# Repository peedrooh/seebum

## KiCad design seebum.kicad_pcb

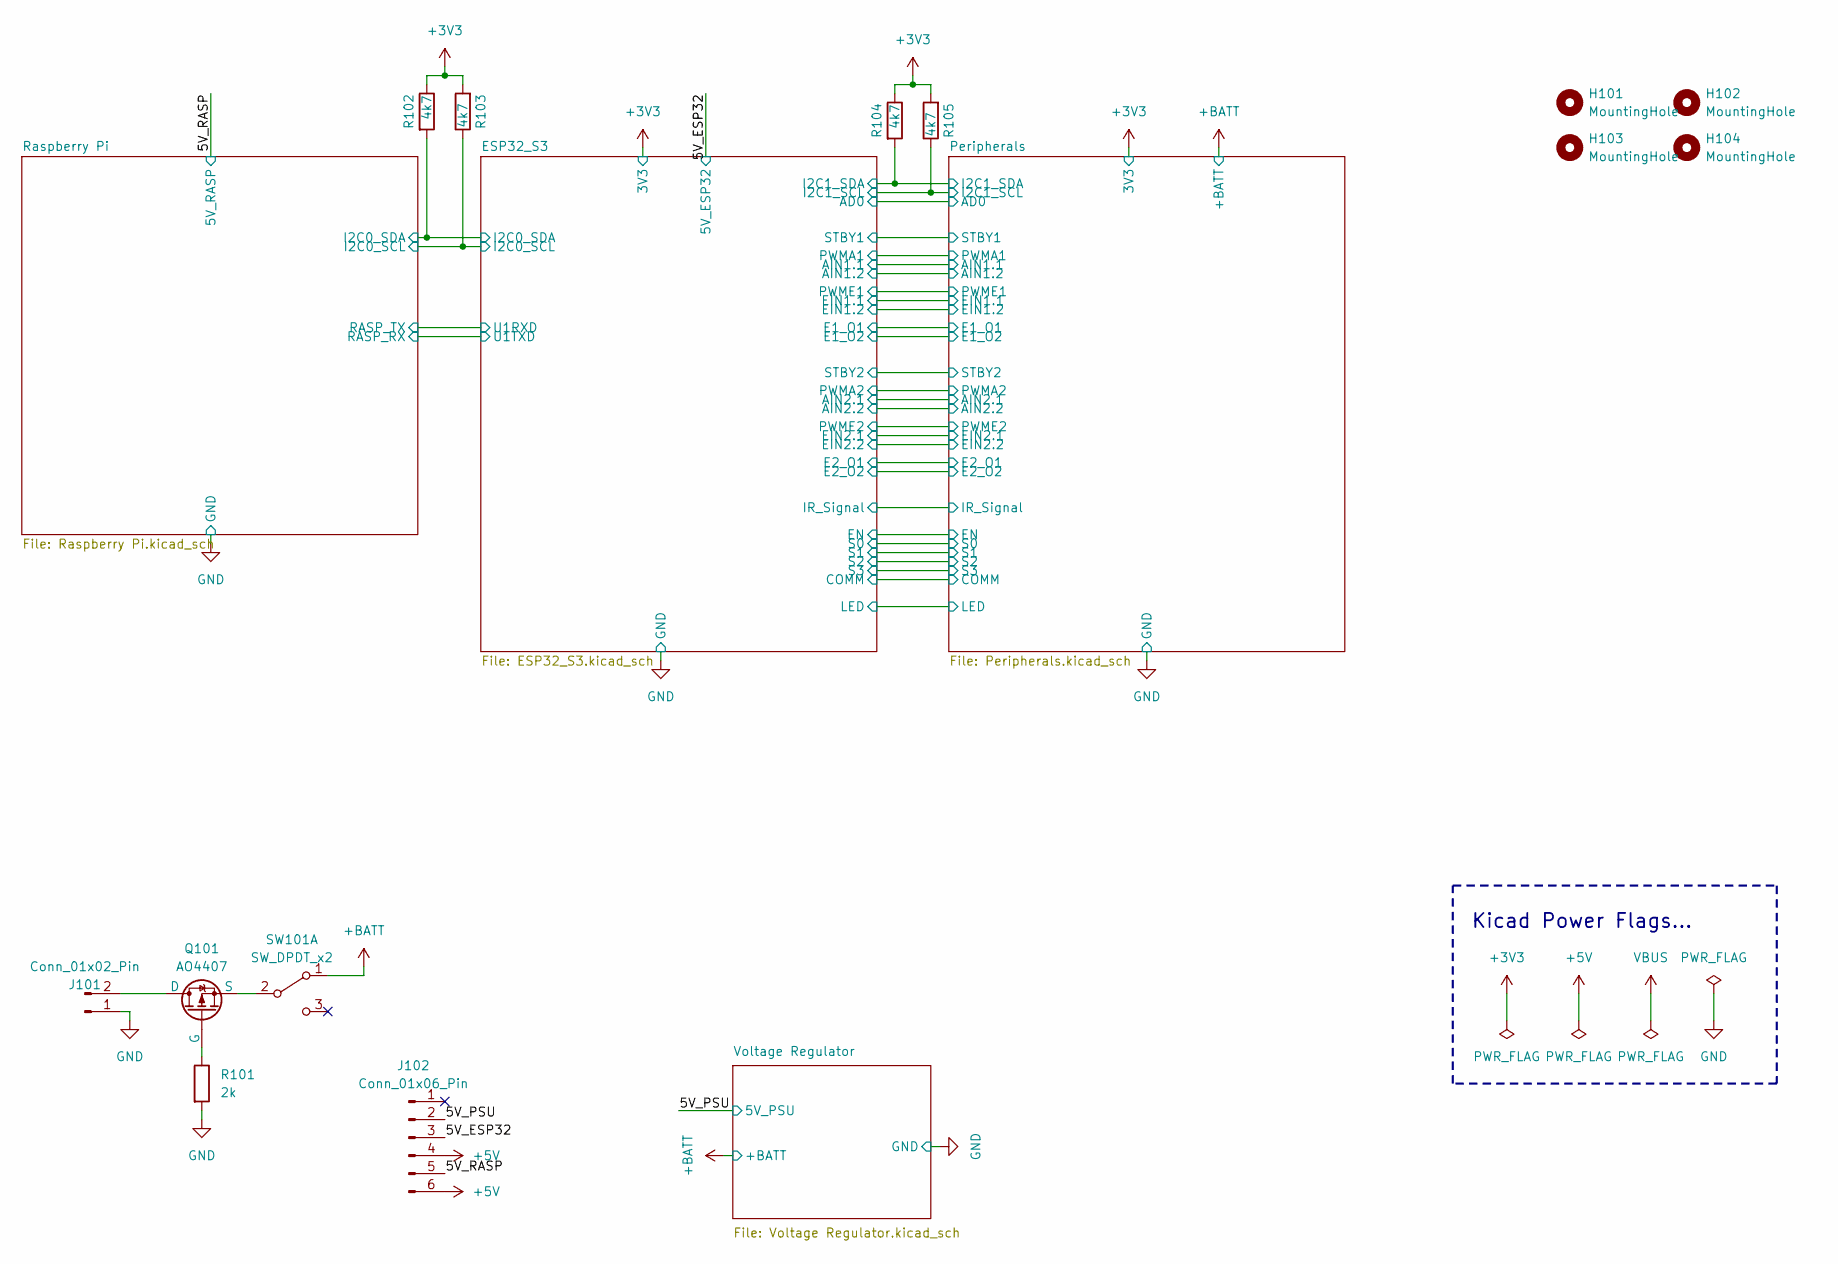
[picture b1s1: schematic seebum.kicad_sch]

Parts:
H101, H102, H103, H104: MountingHole; MountingHole_2.7mm_M2.5_Pad_Via
J101: Conn_01x02_Pin; AMASS_XT30PW-M_1x02_P2.50mm_Horizontal
J102: Conn_01x06_Pin; PinHeader_2x03_P2.54mm_Vertical
Q101: AO4407; SO-8_5.3x6.2mm_P1.27mm; LCSC C469397
R101: 2k; R_0805_2012Metric; LCSC C17604
R102, R103, R104, R105: 4k7; R_0805_2012Metric; LCSC C17673
SW101: SW_DPDT_x2; 5Amp_Switch; LCSC C2884744

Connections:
+3V3: R102.1, R103.2, R104.1, R105.2; also elsewhere on the board
+5V: J102.4, J102.6; also elsewhere on the board
+BATT: SW101.1 (A); also elsewhere on the board
/5V_ESP32: J102.3; also elsewhere on the board
/5V_PSU: J102.2; also elsewhere on the board
/5V_RASP: J102.5; also elsewhere on the board
/ESP32_S3/GPIO6: R102.2; also elsewhere on the board
/ESP32_S3/GPIO7: R103.1; also elsewhere on the board
/Peripherals/SCL: R105.1; also elsewhere on the board
/Peripherals/SDA: R104.2; also elsewhere on the board
GND: J101.1, R101.2; also elsewhere on the board
unnamed: J101.2, Q101.1 (D)
unnamed: Q101.2 (G), R101.1
unnamed: Q101.3 (S), SW101.2 (B)

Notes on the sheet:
Kicad Power Flags...

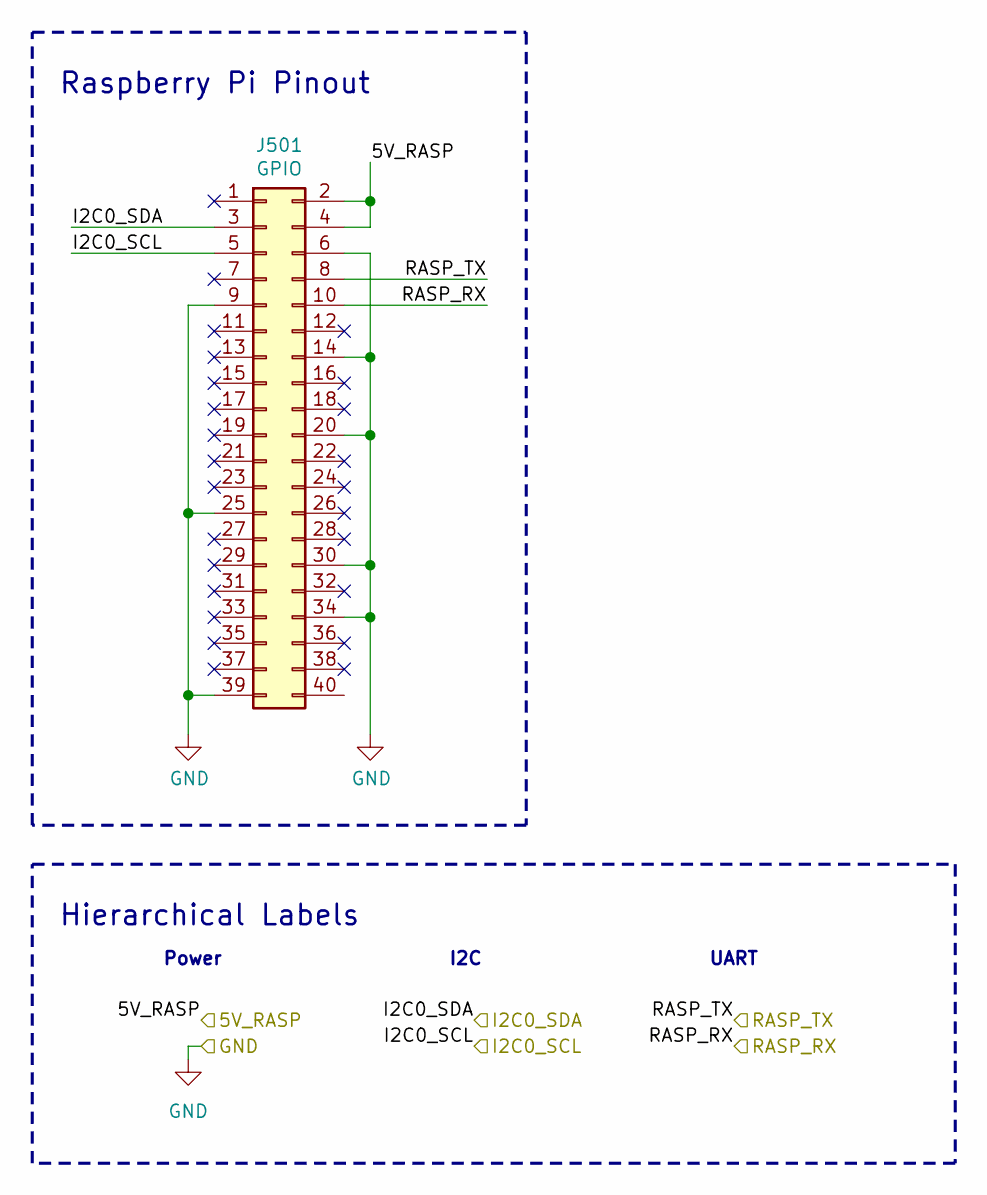
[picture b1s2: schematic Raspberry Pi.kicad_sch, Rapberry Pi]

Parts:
J501: GPIO; PinSocket_2x20_P2.54mm_Vertical

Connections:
/5V_RASP: J501.2, J501.4; also elsewhere on the board
/ESP32_S3/GPIO6: J501.3; also elsewhere on the board
/ESP32_S3/GPIO7: J501.5; also elsewhere on the board
/ESP32_S3/GPIO17: J501.10; also elsewhere on the board
/ESP32_S3/GPIO18: J501.8; also elsewhere on the board
GND: J501.6, J501.9, J501.14, J501.20, J501.25, J501.30, J501.34, J501.39; also elsewhere on the board

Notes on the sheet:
I2C
Hierarchical Labels
UART
Power
Raspberry Pi Pinout

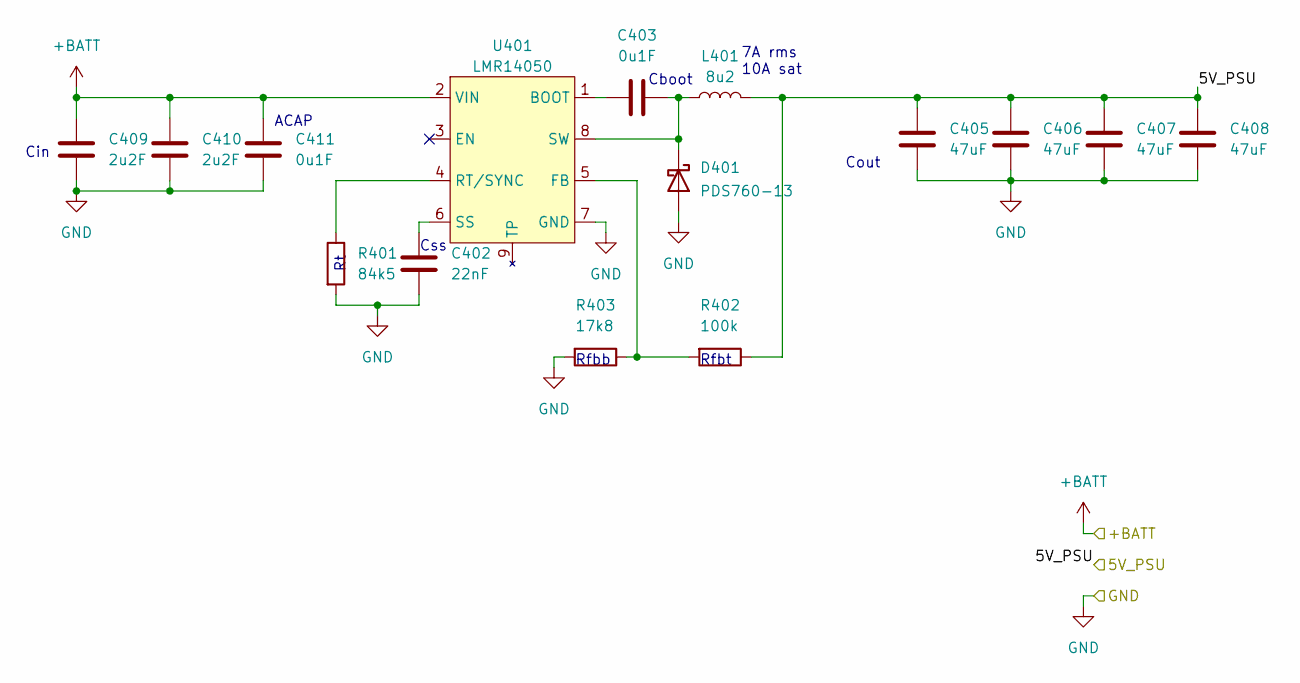
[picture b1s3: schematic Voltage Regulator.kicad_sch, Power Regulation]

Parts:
C402: 22nF; C_0805_2012Metric; LCSC C107137
C403, C411: 0u1F; C_0805_2012Metric; LCSC C89258
C405, C406, C407, C408: 47uF; C_0805_2012Metric; LCSC C7472975
C409, C410: 2u2F; C_1206_3216Metric; LCSC C577211
D401: PDS760-13; D_PowerDI-5; LCSC C96113
L401: 8u2; L_10.4x10.4_H4.8; LCSC C2847563
R401: 84k5; C_0805_2012Metric; LCSC C17842
R402: 100k; R_0805_2012Metric; LCSC C2763792
R403: 17k8; C_0805_2012Metric; LCSC C413729
U401: LMR14050; Texas_R-PDSO-G8_EP2.95x4.9mm_Mask2.4x3.1mm_ThermalVias; LCSC C155484

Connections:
+BATT: C409.1, C410.1, C411.1, U401.2 (VIN); also elsewhere on the board
/5V_PSU: C405.1, C406.1, C407.1, C408.1, L401.2, R402.1; also elsewhere on the board
GND: C402.2, C405.2, C406.2, C407.2, C408.2, C409.2, C410.2, C411.2, D401.2 (A), R401.2, R403.2, U401.7 (GND); also elsewhere on the board
unnamed: C403.2, D401.1 (K), L401.1, U401.8 (SW)
unnamed: C403.1, U401.1 (BOOT)
unnamed: R402.2, R403.1, U401.5 (FB)
unnamed: R401.1, U401.4 (RT/SYNC)
unnamed: C402.1, U401.6 (SS)

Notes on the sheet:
7A rms 10A sat
Cout
Cboot
ACAP
Cin
Css
Rfbt
Rfbb

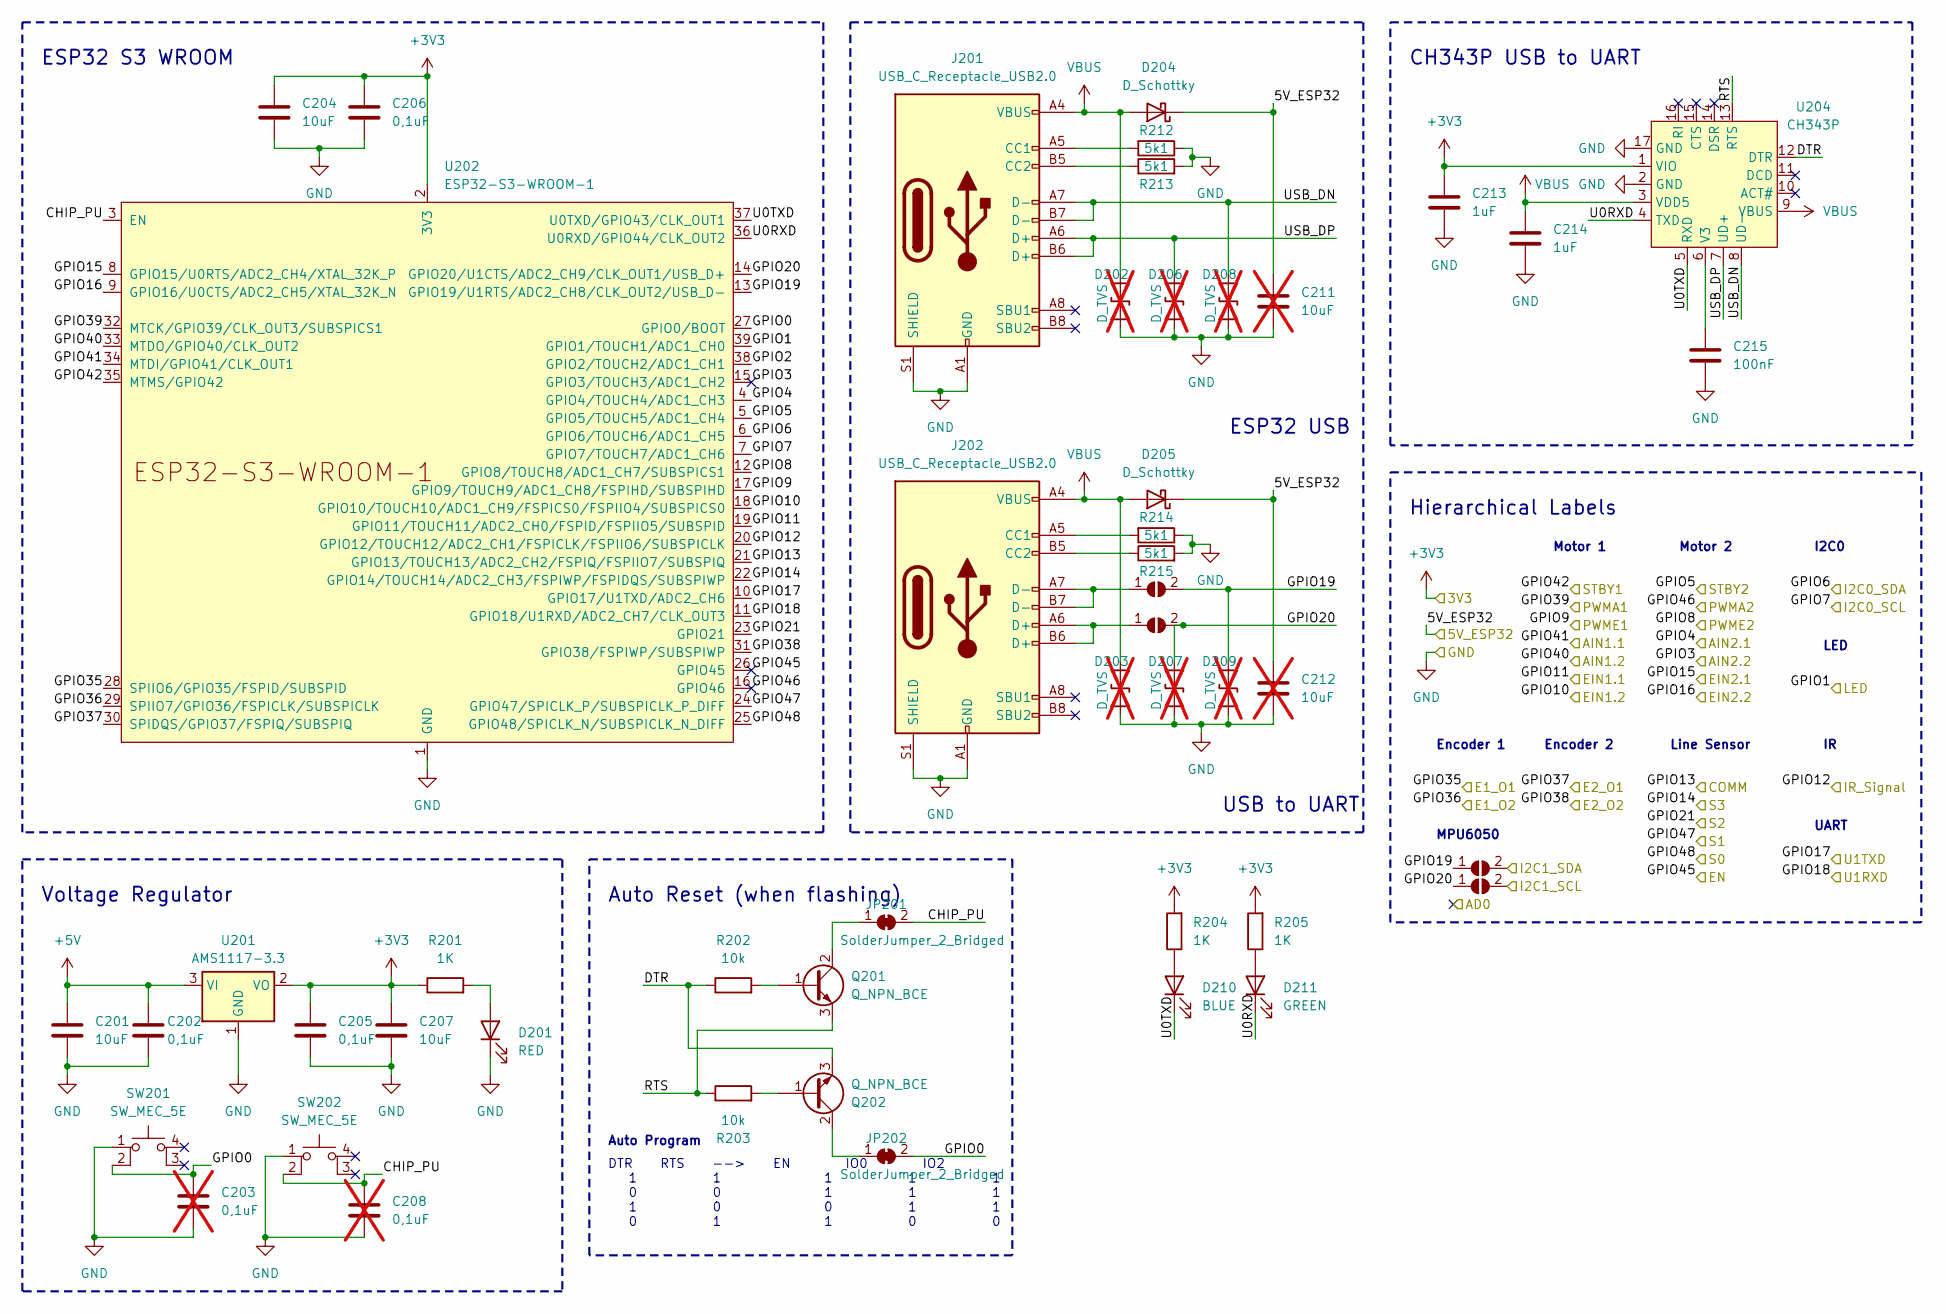
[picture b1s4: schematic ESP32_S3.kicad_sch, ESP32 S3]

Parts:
C201, C204, C207: 10uF; C_0805_2012Metric; LCSC C163225
C202, C205, C206: 0,1uF; C_0805_2012Metric; LCSC C38141
C203, C208: 0,1uF; C_0805_2012Metric; not fitted
C211, C212: 10uF; C_0805_2012Metric; not fitted
C213, C214: 1uF; C_0805_2012Metric; LCSC C28323
C215: 100nF; C_0805_2012Metric; LCSC C38141
D201: RED; LED_0805_2012Metric; LCSC C391863
D202, D203, D206, D207, D208, D209: D_TVS; D_SOD-523; LCSC C383211; not fitted
D204, D205: D_Schottky; D_SOD-123; LCSC C2891704
D210: BLUE; LED_0805_2012Metric; LCSC C205441
D211: GREEN; LED_0805_2012Metric; LCSC C84260
J201, J202: USB_C_Receptacle_USB2.0; USB_C_Receptacle_G-Switch_GT-USB-7010ASV; LCSC C2765186
JP201, JP202: SolderJumper_2_Bridged; SolderJumper-2_P1.3mm_Bridged_RoundedPad1.0x1.5mm
JP203, JP204, JP205, JP206: SolderJumper_2_Open; SolderJumper-2_P1.3mm_Open_TrianglePad1.0x1.5mm
Q201, Q202: Q_NPN_BCE; SOT-23; LCSC C49581
R201, R204, R205: 1K; R_0805_2012Metric; LCSC C17513
R202, R203: 10k; R_0805_2012Metric; LCSC C17414
R212, R213, R214, R215: 5k1; R_0805_2012Metric; LCSC C27834
SW201, SW202: SW_MEC_5E; SW_SPST_B3U-1000P; LCSC C720477
U201: AMS1117-3.3; SOT-223-3_TabPin2; LCSC C347222
U202: ESP32-S3-WROOM-1; LCSC C2913205
U204: CH343P; TQFN-16-1EP_3x3mm_P0.5mm_EP1.23x1.23mm; LCSC C2846043

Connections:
+3V3: C204.1, C205.1, C206.1, C207.1, C213.1, R201.1, R204.2, R205.2, U201.2 (VO), U202.2 (3V3), U204.1 (VIO); also elsewhere on the board
+5V: C201.1, C202.1, U201.3 (VI); also elsewhere on the board
/5V_ESP32: C211.1, C212.1, D204.1 (K), D205.1 (K); also elsewhere on the board
/ESP32_S3/CHIP_PU: C208.1, JP201.2 (B), SW202.2, U202.3 (EN)
/ESP32_S3/DTR: Q202.3 (E), R202.1, U204.12 (DTR)
/ESP32_S3/GPIO0: C203.1, JP202.2 (B), SW201.2, U202.27 (GPIO0/BOOT)
/ESP32_S3/GPIO1: U202.39 (GPIO1/TOUCH1/ADC1_CH0); also elsewhere on the board
/ESP32_S3/GPIO2: U202.38 (GPIO2/TOUCH2/ADC1_CH1)
/ESP32_S3/GPIO3: U202.15 (GPIO3/TOUCH3/ADC1_CH2); also elsewhere on the board
/ESP32_S3/GPIO4: U202.4 (GPIO4/TOUCH4/ADC1_CH3); also elsewhere on the board
/ESP32_S3/GPIO5: U202.5 (GPIO5/TOUCH5/ADC1_CH4); also elsewhere on the board
/ESP32_S3/GPIO6: U202.6 (GPIO6/TOUCH6/ADC1_CH5); also elsewhere on the board
/ESP32_S3/GPIO7: U202.7 (GPIO7/TOUCH7/ADC1_CH6); also elsewhere on the board
/ESP32_S3/GPIO8: U202.12 (GPIO8/TOUCH8/ADC1_CH7/SUBSPICS1); also elsewhere on the board
/ESP32_S3/GPIO9: U202.17 (GPIO9/TOUCH9/ADC1_CH8/FSPIHD/SUBSPIHD); also elsewhere on the board
/ESP32_S3/GPIO10: U202.18 (GPIO10/TOUCH10/ADC1_CH9/FSPICS0/FSPIIO4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); also elsewhere on the board
/ESP32_S3/GPIO11: U202.19 (GPIO11/TOUCH11/ADC2_CH0/FSPID/FSPIIO5/S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); also elsewhere on the board
/ESP32_S3/GPIO12: U202.20 (GPIO12/TOUCH12/ADC2_CH1/FSPICLK/FSPIIO6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); also elsewhere on the board
/ESP32_S3/GPIO13: U202.21 (GPIO13/TOUCH13/ADC2_CH2/FSPIQ/FSPIIO7/S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); also elsewhere on the board
/ESP32_S3/GPIO14: U202.22 (GPIO14/TOUCH14/ADC2_CH3/FSPIWP/FSPIDQS/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); also elsewhere on the board
/ESP32_S3/GPIO15: U202.8 (GPIO15/U0RTS/ADC2_CH4/XTAL_32K_P); also elsewhere on the board
/ESP32_S3/GPIO16: U202.9 (GPIO16/U0CTS/ADC2_CH5/XTAL_32K_N); also elsewhere on the board
/ESP32_S3/GPIO17: U202.10 (GPIO17/U1TXD/ADC2_CH6); also elsewhere on the board
/ESP32_S3/GPIO18: U202.11 (GPIO18/U1RXD/ADC2_CH7/CLK_OUT3); also elsewhere on the board
/ESP32_S3/GPIO19: D209.2 (A2), JP203.2 (B), JP205.1 (A), U202.13 (GPIO19/U1RTS/ADC2_CH8/CLK_OUT2/USB_D-)
/ESP32_S3/GPIO20: D207.1 (A1), JP204.2 (B), JP206.1 (A), U202.14 (GPIO20/U1CTS/ADC2_CH9/CLK_OUT1/USB_D+)
/ESP32_S3/GPIO21: U202.23 (GPIO21); also elsewhere on the board
/ESP32_S3/GPIO35: U202.28 (SPIIO6/GPIO35/FSPID/SUBSPID); also elsewhere on the board
/ESP32_S3/GPIO36: U202.29 (SPIIO7/GPIO36/FSPICLK/SUBSPICLK); also elsewhere on the board
/ESP32_S3/GPIO37: U202.30 (SPIDQS/GPIO37/FSPIQ/SUBSPIQ); also elsewhere on the board
/ESP32_S3/GPIO38: U202.31 (GPIO38/FSPIWP/SUBSPIWP); also elsewhere on the board
/ESP32_S3/GPIO39: U202.32 (MTCK/GPIO39/CLK_OUT3/SUBSPICS1); also elsewhere on the board
/ESP32_S3/GPIO40: U202.33 (MTDO/GPIO40/CLK_OUT2); also elsewhere on the board
/ESP32_S3/GPIO41: U202.34 (MTDI/GPIO41/CLK_OUT1); also elsewhere on the board
/ESP32_S3/GPIO42: U202.35 (MTMS/GPIO42); also elsewhere on the board
/ESP32_S3/GPIO45: U202.26 (GPIO45); also elsewhere on the board
/ESP32_S3/GPIO46: U202.16 (GPIO46); also elsewhere on the board
/ESP32_S3/GPIO47: U202.24 (GPIO47/SPICLK_P/SUBSPICLK_P_DIFF); also elsewhere on the board
/ESP32_S3/GPIO48: U202.25 (GPIO48/SPICLK_N/SUBSPICLK_N_DIFF); also elsewhere on the board
/ESP32_S3/RTS: Q201.3 (E), R203.1, U204.13 (RTS)
/ESP32_S3/U0RXD: D211.1 (K), U202.36 (U0RXD/GPIO44/CLK_OUT2), U204.4 (TXD)
/ESP32_S3/U0TXD: D210.1 (K), U202.37 (U0TXD/GPIO43/CLK_OUT1), U204.5 (RXD)
/ESP32_S3/USB_DN: D208.2 (A2), J201.A7 (D-), J201.B7 (D-), U204.8 (UD-)
/ESP32_S3/USB_DP: D206.1 (A1), J201.A6 (D+), J201.B6 (D+), U204.7 (UD+)
/Peripherals/SCL: JP206.2 (B); also elsewhere on the board
/Peripherals/SDA: JP205.2 (B); also elsewhere on the board
GND: C201.2, C202.2, C203.2, C204.2, C205.2, C206.2, C207.2, C208.2, C211.2, C212.2, C213.2, C214.2, C215.2, D201.1 (K), D202.1 (A1), D203.1 (A1), D206.2 (A2), D207.2 (A2), D208.1 (A1), D209.1 (A1), J201.A1 (GND), J201.A12 (GND), J201.B1 (GND), J201.B12 (GND), J201.S1 (SHIELD), J202.A1 (GND), J202.A12 (GND), J202.B1 (GND), J202.B12 (GND), J202.S1 (SHIELD), R212.1, R213.2, R214.1, R215.2, SW201.1, SW202.1, U201.1 (GND), U202.1 (GND), U202.40 (GND), U202.41 (GND), U204.2 (GND), U204.17 (GND); also elsewhere on the board
unnamed: D201.2 (A), R201.2
unnamed: D210.2 (A), R204.1
unnamed: D211.2 (A), R205.1
unnamed: J201.A5 (CC1), R212.2
unnamed: J201.B5 (CC2), R213.1
unnamed: J202.A5 (CC1), R214.2
unnamed: J202.B5 (CC2), R215.1
unnamed: JP201.1 (A), Q201.2 (C)
unnamed: JP202.1 (A), Q202.2 (C)
unnamed: J202.A7 (D-), J202.B7 (D-), JP203.1 (A)
unnamed: J202.A6 (D+), J202.B6 (D+), JP204.1 (A)
unnamed: Q201.1 (B), R202.2
unnamed: Q202.1 (B), R203.2
unnamed: C215.1, U204.6 (V3)
VBUS: C214.1, D202.2 (A2), D203.2 (A2), D204.2 (A), D205.2 (A), J201.A4 (VBUS), J201.A9 (VBUS), J201.B4 (VBUS), J201.B9 (VBUS), J202.A4 (VBUS), J202.A9 (VBUS), J202.B4 (VBUS), J202.B9 (VBUS), U204.3 (VDD5), U204.9 (VBUS)

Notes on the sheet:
Voltage Regulator
ESP32 S3 WROOM
DTR RTS --> EN IO0 IO2 1 1 1 1 1 0 0 1 1 1 1 0 0 1 1 0 1 1 0 0
MPU6050
Motor 1
Auto Program
Line Sensor
USB to UART
UART
Encoder 1
ESP32 USB
Auto Reset (when flashing)
CH343P USB to UART
Hierarchical Labels
Encoder 2
Motor 2
I2C0
LED

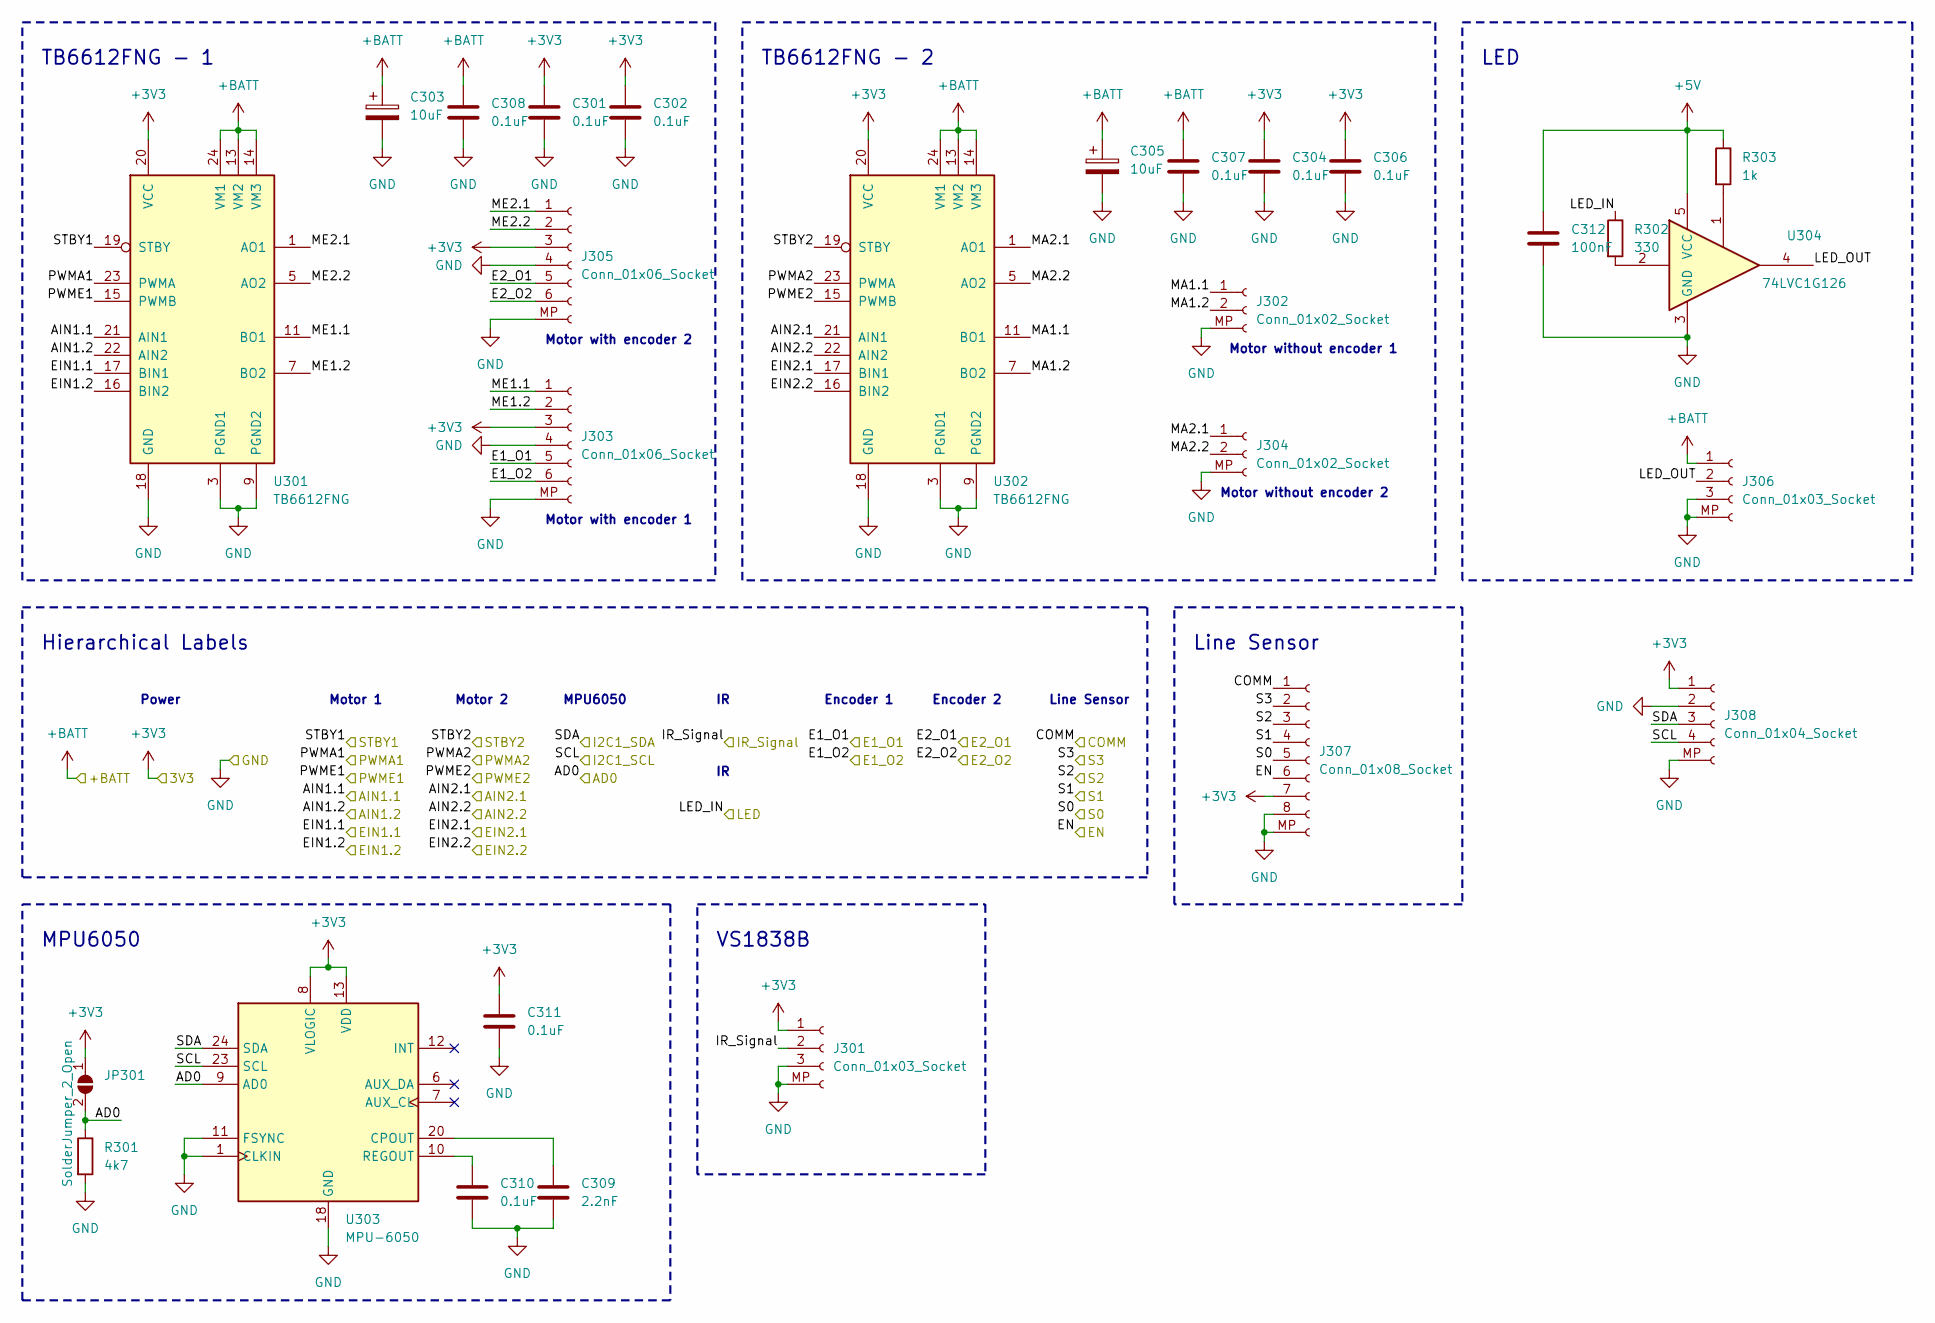
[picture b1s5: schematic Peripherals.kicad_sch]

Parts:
C301, C302, C304, C306, C307, C308, C310, C311: 0.1uF; C_0805_2012Metric; LCSC C38141
C303, C305: 10uF; CP_EIA-3528-21_Kemet-B; LCSC C163225
C309: 2.2nF; C_0805_2012Metric; LCSC C36576
C312: 100nF; C_0805_2012Metric; LCSC C38141
J301, J306: Conn_01x03_Socket; JST_PH_B3B-PH-SM4-TB_1x03-1MP_P2.00mm_Vertical; LCSC C160353
J302, J304: Conn_01x02_Socket; JST_PH_S2B-PH-SM4-TB_1x02-1MP_P2.00mm_Horizontal; LCSC C295747
J303, J305: Conn_01x06_Socket; JST_PH_S6B-PH-SM4-TB_1x06-1MP_P2.00mm_Horizontal; LCSC C265405
J307: Conn_01x08_Socket; JST_PH_B8B-PH-SM4-TB_1x08-1MP_P2.00mm_Vertical; LCSC C157915
J308: Conn_01x04_Socket; JST_PH_B4B-PH-SM4-TB_1x04-1MP_P2.00mm_Vertical
JP301: SolderJumper_2_Open; SolderJumper-2_P1.3mm_Open_TrianglePad1.0x1.5mm
R301: 4k7; R_0805_2012Metric; LCSC C17673
R302: 330; R_0805_2012Metric; LCSC C17630
R303: 1k; R_0805_2012Metric; LCSC C17513
U301, U302: TB6612FNG; SSOP-24_5.3x8.2mm_P0.65mm; LCSC C88224
U303: MPU-6050; InvenSense_QFN-24_4x4mm_P0.5mm; LCSC C24112
U304: 74LVC1G126; SOT-23-5; LCSC C7834

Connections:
+3V3: C301.1, C302.1, C304.1, C306.1, C311.1, J301.1, J303.3, J305.3, J307.7, J308.1, JP301.1 (A), U301.20 (VCC), U302.20 (VCC), U303.8 (VLOGIC), U303.13 (VDD); also elsewhere on the board
+5V: C312.1, R303.1, U304.5 (VCC); also elsewhere on the board
+BATT: C303.1, C305.1, C307.1, C308.1, J306.1, U301.13 (VM2), U301.14 (VM3), U301.24 (VM1), U302.13 (VM2), U302.14 (VM3), U302.24 (VM1); also elsewhere on the board
/ESP32_S3/GPIO1: R302.1; also elsewhere on the board
/ESP32_S3/GPIO3: U302.22 (AIN2); also elsewhere on the board
/ESP32_S3/GPIO4: U302.21 (AIN1); also elsewhere on the board
/ESP32_S3/GPIO5: U302.19 (STBY); also elsewhere on the board
/ESP32_S3/GPIO8: U302.15 (PWMB); also elsewhere on the board
/ESP32_S3/GPIO9: U301.15 (PWMB); also elsewhere on the board
/ESP32_S3/GPIO10: U301.16 (BIN2); also elsewhere on the board
/ESP32_S3/GPIO11: U301.17 (BIN1); also elsewhere on the board
/ESP32_S3/GPIO12: J301.2; also elsewhere on the board
/ESP32_S3/GPIO13: J307.1; also elsewhere on the board
/ESP32_S3/GPIO14: J307.2; also elsewhere on the board
/ESP32_S3/GPIO15: U302.17 (BIN1); also elsewhere on the board
/ESP32_S3/GPIO16: U302.16 (BIN2); also elsewhere on the board
/ESP32_S3/GPIO21: J307.3; also elsewhere on the board
/ESP32_S3/GPIO35: J303.5; also elsewhere on the board
/ESP32_S3/GPIO36: J303.6; also elsewhere on the board
/ESP32_S3/GPIO37: J305.5; also elsewhere on the board
/ESP32_S3/GPIO38: J305.6; also elsewhere on the board
/ESP32_S3/GPIO39: U301.23 (PWMA); also elsewhere on the board
/ESP32_S3/GPIO40: U301.22 (AIN2); also elsewhere on the board
/ESP32_S3/GPIO41: U301.21 (AIN1); also elsewhere on the board
/ESP32_S3/GPIO42: U301.19 (STBY); also elsewhere on the board
/ESP32_S3/GPIO45: J307.6; also elsewhere on the board
/ESP32_S3/GPIO46: U302.23 (PWMA); also elsewhere on the board
/ESP32_S3/GPIO47: J307.4; also elsewhere on the board
/ESP32_S3/GPIO48: J307.5; also elsewhere on the board
/Peripherals/AD0: JP301.2 (B), R301.1, U303.9 (AD0)
/Peripherals/LED_OUT: J306.2, U304.4
/Peripherals/MA1.1: J302.1, U302.11 (BO1), U302.12 (BO1)
/Peripherals/MA1.2: J302.2, U302.7 (BO2), U302.8 (BO2)
/Peripherals/MA2.1: J304.1, U302.1 (AO1), U302.2 (AO1)
/Peripherals/MA2.2: J304.2, U302.5 (AO2), U302.6 (AO2)
/Peripherals/ME1.1: J303.1, U301.11 (BO1), U301.12 (BO1)
/Peripherals/ME1.2: J303.2, U301.7 (BO2), U301.8 (BO2)
/Peripherals/ME2.1: J305.1, U301.1 (AO1), U301.2 (AO1)
/Peripherals/ME2.2: J305.2, U301.5 (AO2), U301.6 (AO2)
/Peripherals/SCL: J308.4, U303.23 (SCL); also elsewhere on the board
/Peripherals/SDA: J308.3, U303.24 (SDA); also elsewhere on the board
GND: C301.2, C302.2, C303.2, C304.2, C305.2, C306.2, C307.2, C308.2, C309.2, C310.2, C311.2, C312.2, J301.3, J301.MP (Pin_4), J302.MP (Pin_3), J303.4, J303.MP (Pin_7), J304.MP (Pin_3), J305.4, J305.MP (Pin_7), J306.3, J306.MP (Pin_4), J307.8, J307.MP (Pin_9), J308.2, J308.MP (Pin_5), R301.2, U301.3 (PGND1), U301.4 (PGND1), U301.9 (PGND2), U301.10 (PGND2), U301.18 (GND), U302.3 (PGND1), U302.4 (PGND1), U302.9 (PGND2), U302.10 (PGND2), U302.18 (GND), U303.1 (CLKIN), U303.11 (FSYNC), U303.18 (GND), U304.3 (GND); also elsewhere on the board
unnamed: R302.2, U304.2
unnamed: R303.2, U304.1
unnamed: C309.1, U303.20 (CPOUT)
unnamed: C310.1, U303.10 (REGOUT)

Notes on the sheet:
MPU6050
Motor without encoder 1
Line Sensor
Motor 2
Hierarchical Labels
Motor 1
Encoder 1
Motor without encoder 2
Motor with encoder 2
TB6612FNG - 2
TB6612FNG - 1
Encoder 2
Power
LED
VS1838B
Motor with encoder 1

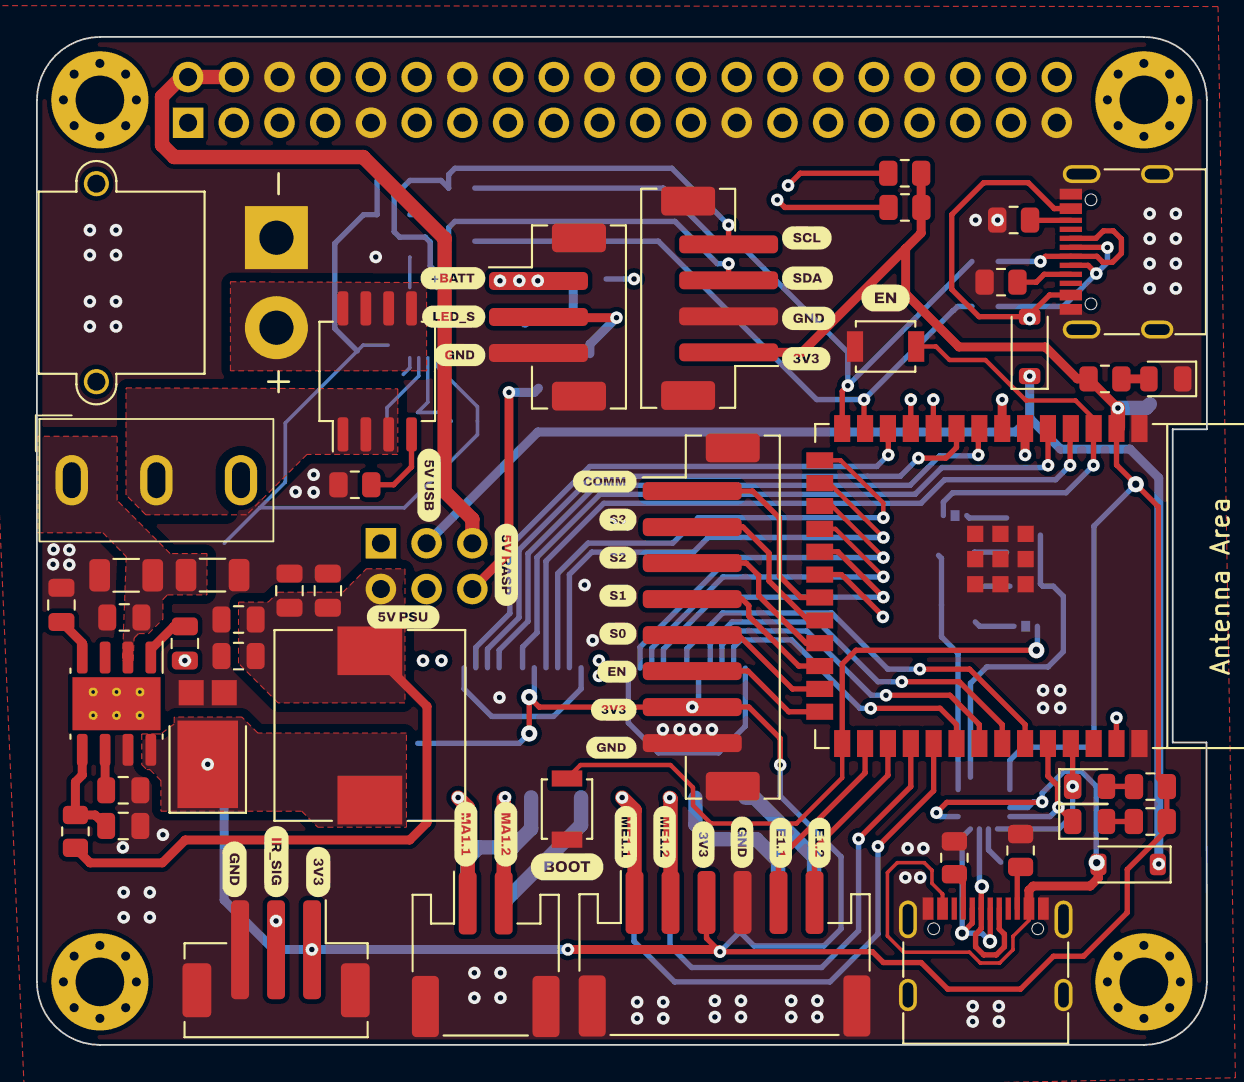
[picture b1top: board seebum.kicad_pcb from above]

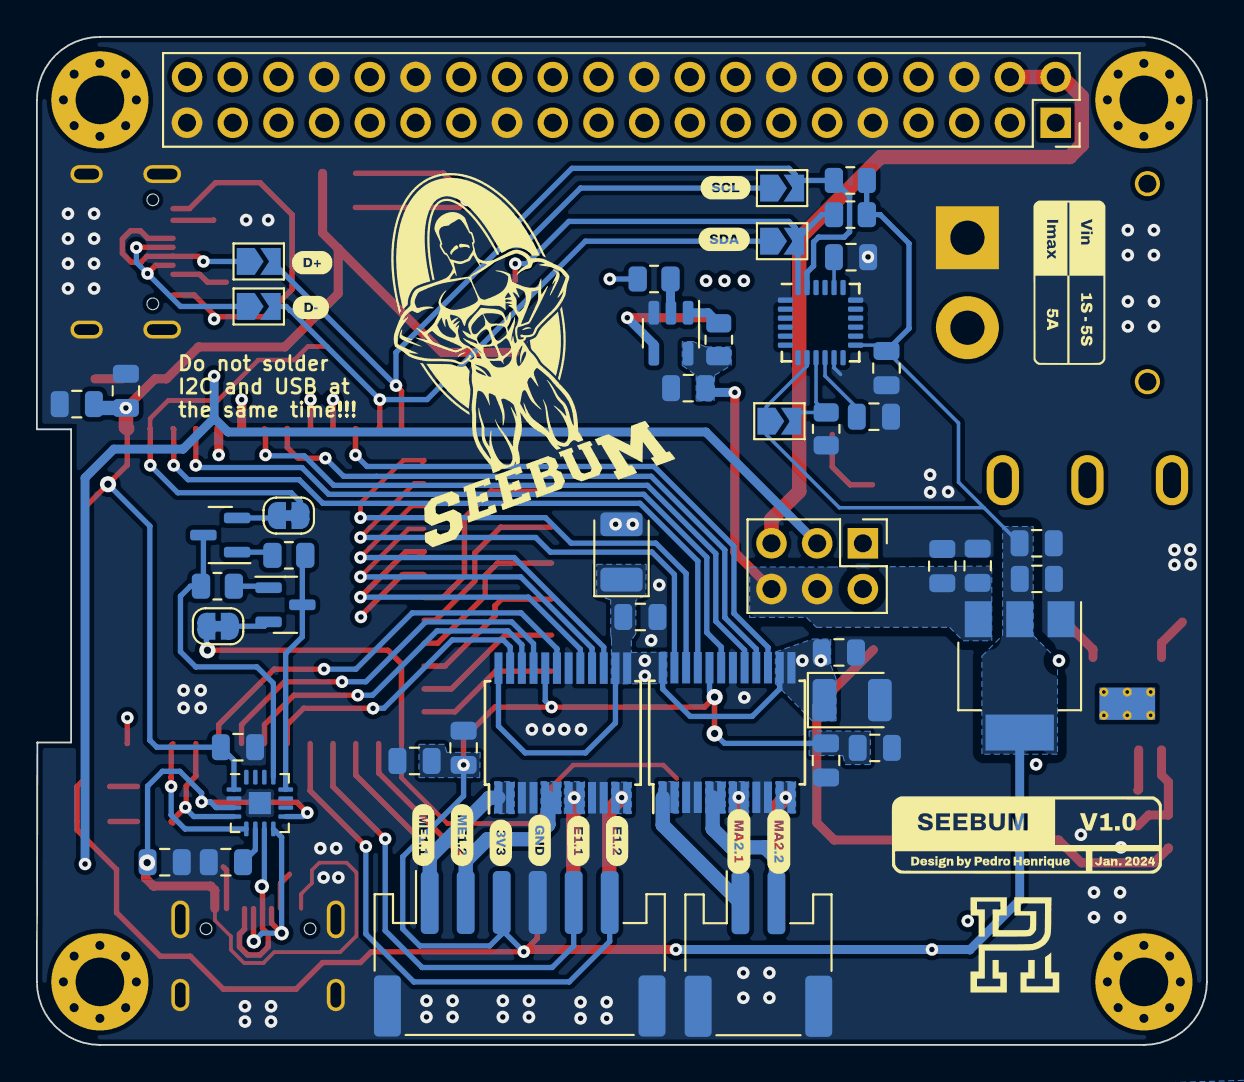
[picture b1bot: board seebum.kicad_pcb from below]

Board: 4 copper layers, 65.0 x 56.0 mm, 95 parts (47 on the bottom side), 86 nets.

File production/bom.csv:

Designator,Footprint,Quantity,Value,LCSC Part #
"C201, C204, C207",805,3,10uF,C163225
"C202, C205, C206",805,3,"0,1uF",C38141
"C213, C214",805,2,1uF,C28323
"C215, C312",805,2,100nF,C38141
"C301, C302, C304, C306, C307, C308, C310, C311",805,8,0.1uF,C38141
"C303, C305",CP_EIA-3528-21_Kemet-B,2,10uF,C163225
C309,805,1,2.2nF,C36576
C402,805,1,22nF,C107137
"C403, C411",805,2,0u1F,C89258
"C405, C406, C407, C408",805,4,47uF,C7472975
"C409, C410",1206,2,2u2F,C577211
D201,805,1,RED,C391863
"D204, D205",D_SOD-123,2,D_Schottky,C2891704
D210,805,1,BLUE,C205441
D211,805,1,GREEN,C84260
D401,D_PowerDI-5,1,PDS760-13,C96113
"J201, J202",USB_C_Receptacle_G-Switch_GT-USB-7010ASV,2,USB_C_Receptacle_USB2.0,C2765186
"J301, J306",JST_PH_B3B-PH-SM4-TB_1x03-1MP_P2.00mm_Vertical,2,Conn_01x03_Socket,C160353
"J302, J304",JST_PH_S2B-PH-SM4-TB_1x02-1MP_P2.00mm_Horizontal,2,Conn_01x02_Socket,C295747
"J303, J305",JST_PH_S6B-PH-SM4-TB_1x06-1MP_P2.00mm_Horizontal,2,Conn_01x06_Socket,C265405
J307,JST_PH_B8B-PH-SM4-TB_1x08-1MP_P2.00mm_Vertical,1,Conn_01x08_Socket,C157915
L401,L_10.4x10.4_H4.8,1,8u2,C2847563
Q101,SO-8_5.3x6.2mm_P1.27mm,1,AO4407,C469397
"Q201, Q202",SOT-23,2,Q_NPN_BCE,C49581
R101,805,1,2k,C17604
"R102, R103, R104, R105, R301",805,5,4k7,C17673
"R201, R204, R205, R303",805,4,1K,C17513
"R202, R203",805,2,10k,C17414
"R212, R213, R214, R215",805,4,5k1,C27834
R302,805,1,330,C17630
R401,805,1,84k5,C17842
R402,805,1,100k,C2763792
R403,805,1,17k8,C413729
SW101,5Amp_Switch,1,SW_DPDT_x2,C2884744
"SW201, SW202",SW_SPST_B3U-1000P,2,SW_MEC_5E,C720477
U201,SOT-223-3_TabPin2,1,AMS1117-3.3,C347222
U202,ESP32-S3-WROOM-1,1,ESP32-S3-WROOM-1,C2913205
U204,TQFN-16-1EP_3x3mm_P0.5mm_EP1.23x1.23mm,1,CH343P,C2846043
"U301, U302",SSOP-24_5.3x8.2mm_P0.65mm,2,TB6612FNG,C88224
U303,InvenSense_QFN-24_4x4mm_P0.5mm,1,MPU-6050,C24112
U304,SOT-23-5,1,74LVC1G126,C7834
U401,Texas_R-PDSO-G8_EP2.95x4.9mm_Mask2.4x3.1mm_ThermalVias,1,LMR14050,C155484
